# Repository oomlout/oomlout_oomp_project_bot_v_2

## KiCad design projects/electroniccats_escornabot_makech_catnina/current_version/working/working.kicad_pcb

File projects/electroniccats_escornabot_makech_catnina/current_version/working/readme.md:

# escornabot_makech
 
## summary 
* id: electroniccats_escornabot_makech_catnina
* user: electroniccats
* name: escornabot_makech
* board: catnina
* repo: https://github.com/ElectronicCats/Escornabot-Makech
* src_file_repo_kicad_pcb: Makech/Expansion NINA/CatNINA.kicad_pcb
* src_file_repo_kicad_pcb_link: https://github.com/ElectronicCats/Escornabot-Makech/tree/master/Makech/Expansion NINA/CatNINA.kicad_pcb

* src_file_repo_sch: Makech/Expansion NINA/CatNINA.sch
* src_file_repo_sch_link: https://github.com/ElectronicCats/Escornabot-Makech/tree/master/Makech/Expansion NINA/CatNINA.sch
* full details link: https://github.com/oomlout/oomlout_oomp_project_bot_v_2/tree/main/projects/electroniccats_escornabot_makech_catnina/current_version/working

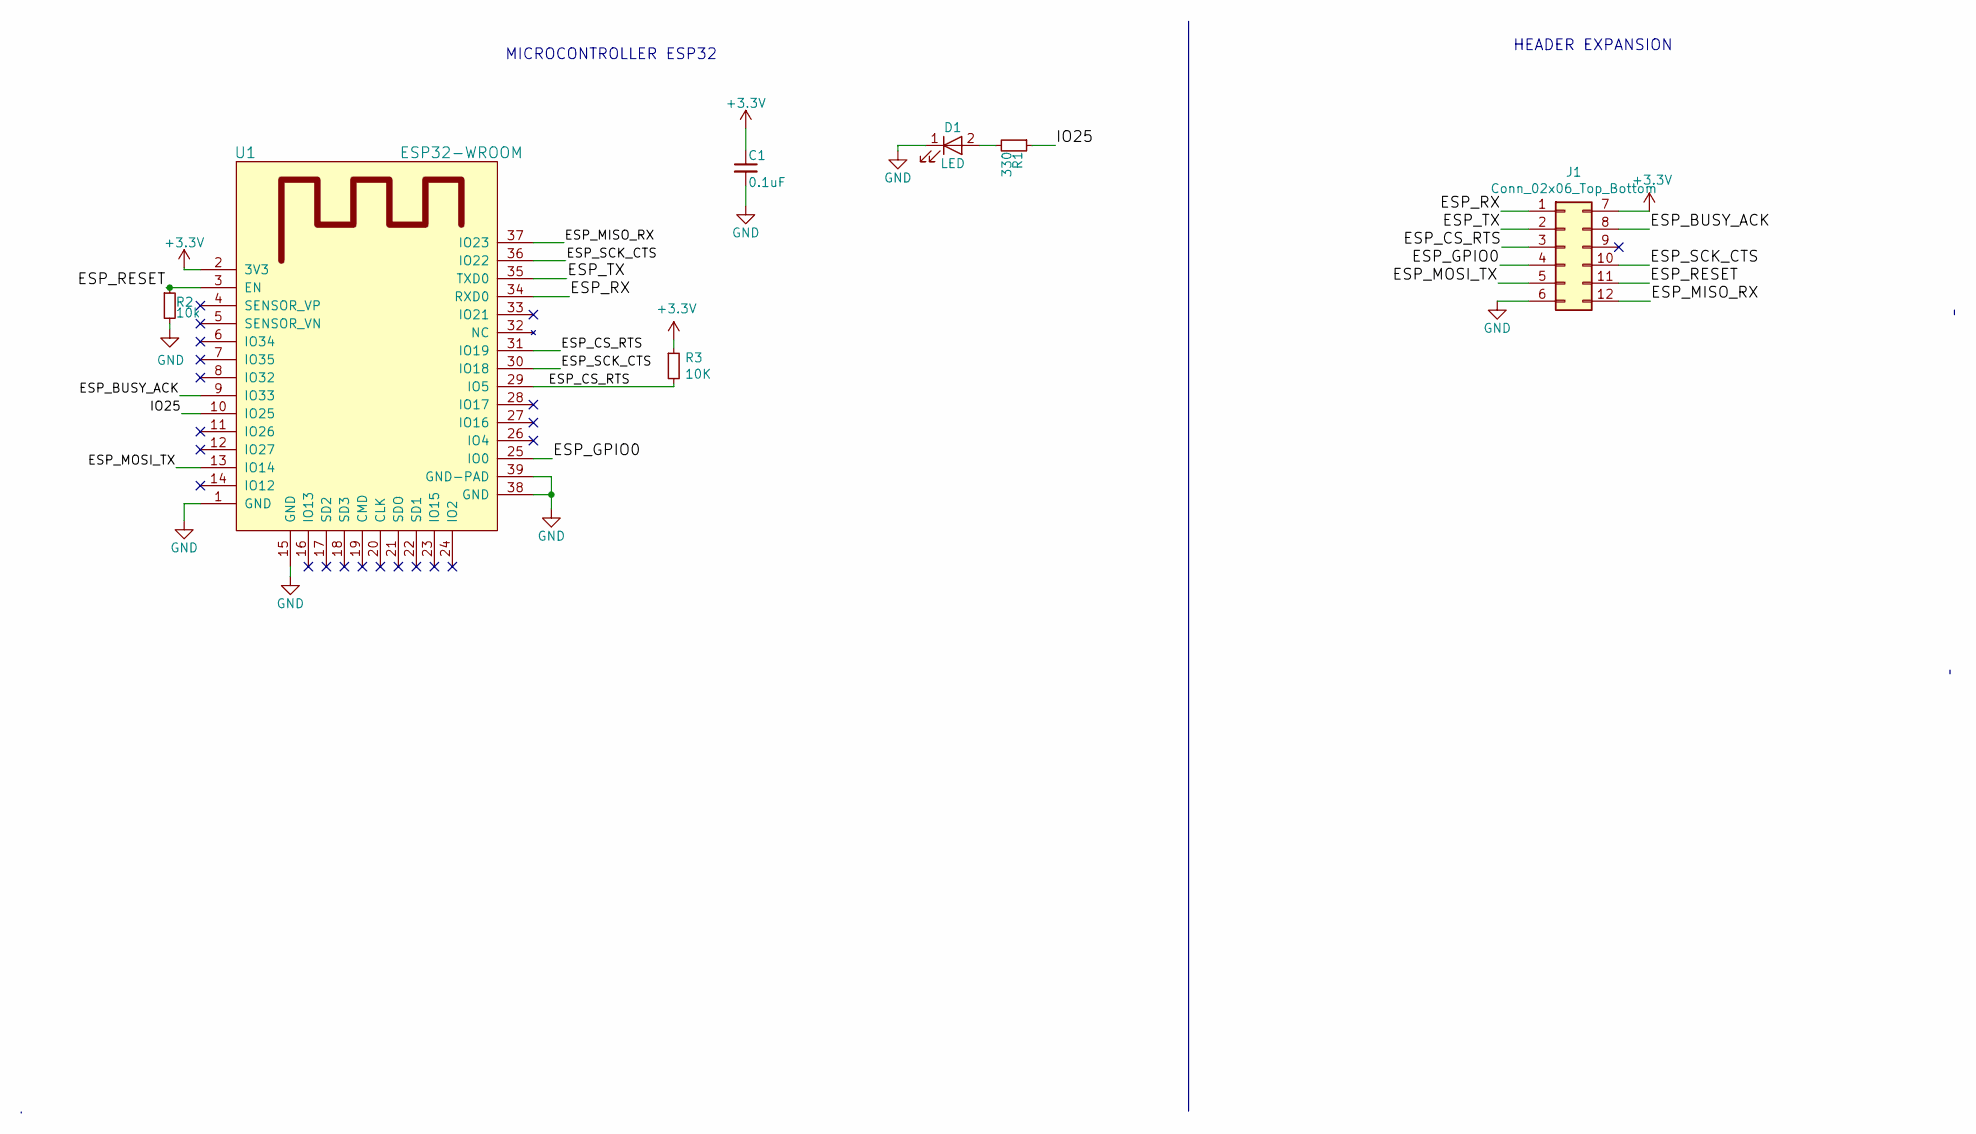
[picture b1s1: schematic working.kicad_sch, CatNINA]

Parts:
C1: 0.1uF; C_0805_HandSoldering
D1: LED; LED_0805_HandSoldering
J1: Conn_02x06_Top_Bottom; 61301221121
R1: 330; R_0805_HandSoldering
R2: 10k; R_0805_HandSoldering
R3: 10K; R_0805_HandSoldering
U1: ESP32-WROOM

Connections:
+3V3: C1.1, J1.7, R3.1, U1.2 (3V3)
/ESP_BUSY_ACK: J1.8, U1.9 (IO33)
/ESP_CS_RTS: J1.3, R3.2, U1.29 (IO5), U1.31 (IO19)
/ESP_GPIO0: J1.4, U1.25 (IO0)
/ESP_MISO_RX: J1.12, U1.37 (IO23)
/ESP_MOSI_TX: J1.5, U1.13 (IO14)
/ESP_RESET: J1.11, R2.1, U1.3 (EN)
/ESP_RX: J1.1, U1.34 (RXD0)
/ESP_SCK_CTS: J1.10, U1.30 (IO18), U1.36 (IO22)
/ESP_TX: J1.2, U1.35 (TXD0)
/IO25: R1.1, U1.10 (IO25)
GND: C1.2, D1.1 (K), J1.6, R2.2, U1.1 (GND), U1.15 (GND), U1.38 (GND), U1.39 (GND-PAD)
unnamed: D1.2 (A), R1.2

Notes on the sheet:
MICROCONTROLLER ESP32
HEADER EXPANSION

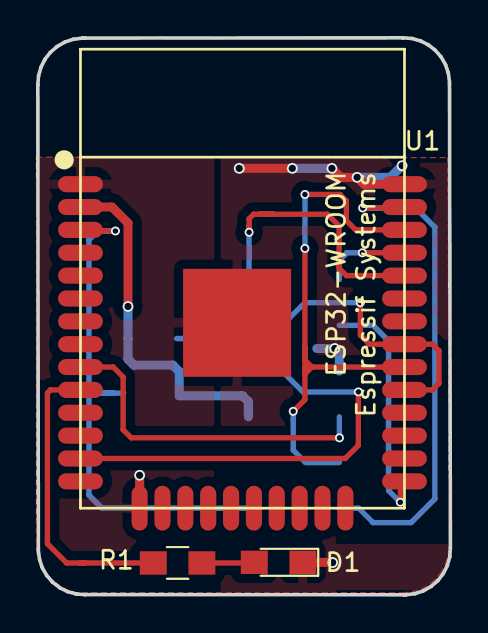
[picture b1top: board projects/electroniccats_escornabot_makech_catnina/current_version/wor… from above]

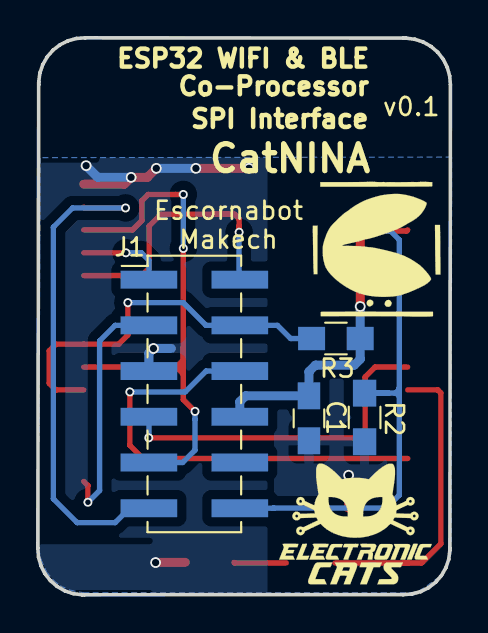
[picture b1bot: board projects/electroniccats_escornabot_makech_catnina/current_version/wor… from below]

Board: 2 copper layers, 22.9 x 30.9 mm, 7 parts (4 on the bottom side), 13 nets.

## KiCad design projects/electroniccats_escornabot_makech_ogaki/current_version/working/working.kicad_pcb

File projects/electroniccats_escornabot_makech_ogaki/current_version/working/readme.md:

# escornabot_makech
 
## summary 
* id: electroniccats_escornabot_makech_ogaki
* user: electroniccats
* name: escornabot_makech
* board: ogaki
* repo: https://github.com/ElectronicCats/Escornabot-Makech
* src_file_repo_kicad_pcb: Ogaki/hardware/KiCad files/Ogaki.kicad_pcb
* src_file_repo_kicad_pcb_link: https://github.com/ElectronicCats/Escornabot-Makech/tree/master/Ogaki/hardware/KiCad files/Ogaki.kicad_pcb

* src_file_repo_sch: Ogaki/hardware/KiCad files/Ogaki.sch
* src_file_repo_sch_link: https://github.com/ElectronicCats/Escornabot-Makech/tree/master/Ogaki/hardware/KiCad files/Ogaki.sch
* full details link: https://github.com/oomlout/oomlout_oomp_project_bot_v_2/tree/main/projects/electroniccats_escornabot_makech_ogaki/current_version/working

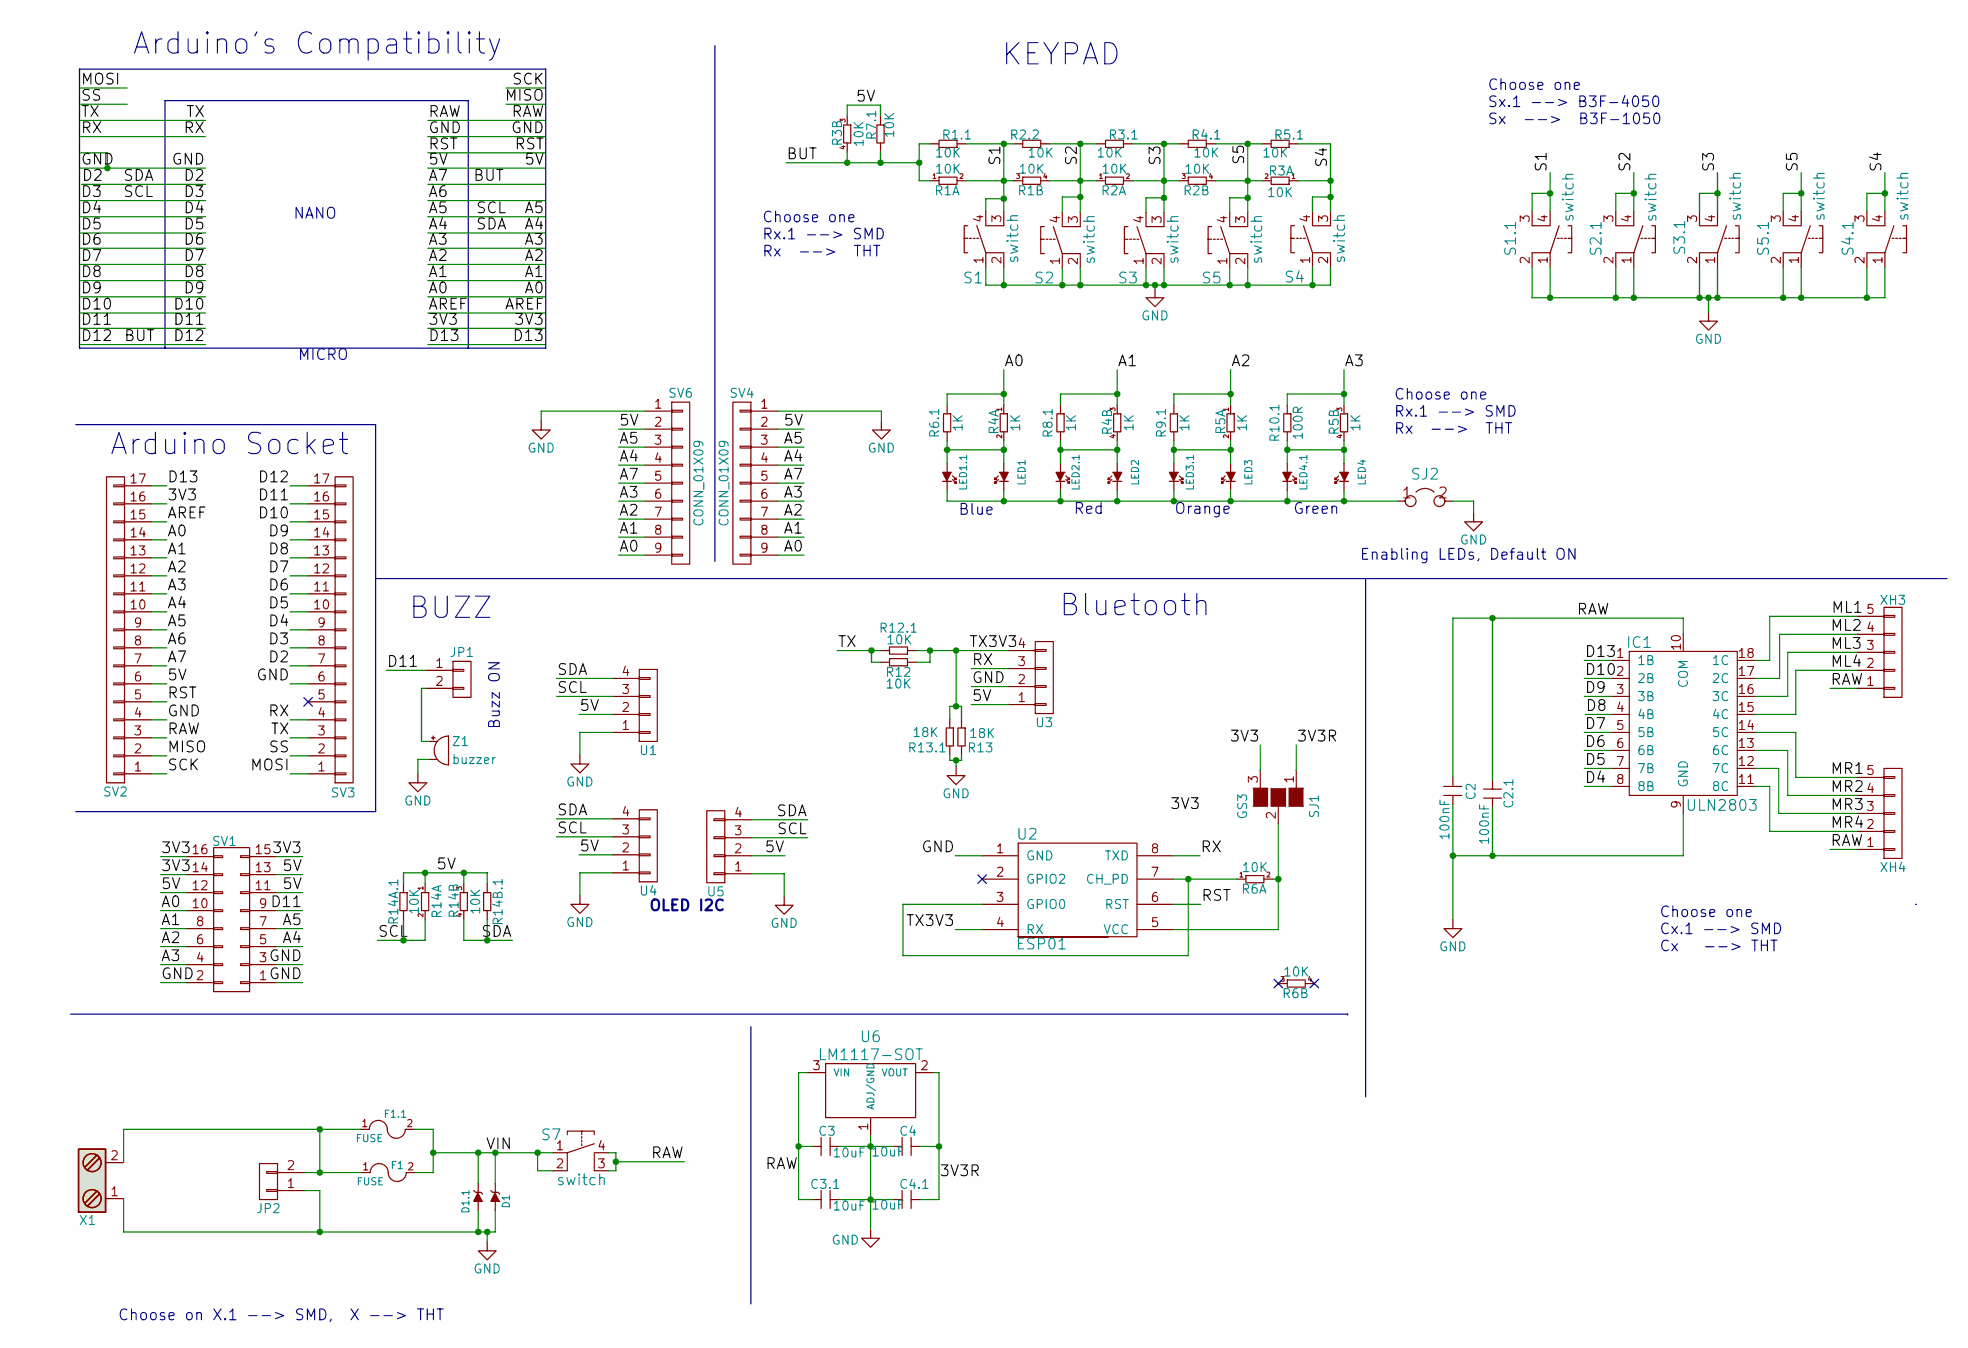
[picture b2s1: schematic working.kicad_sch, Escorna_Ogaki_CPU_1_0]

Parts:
C2: 100nF; C_Disc_D5.0mm_W2.5mm_P5.00mm
C2.1: 100nF; C_0603_HandSoldering
C3, C4: 10uF; C_Disc_D5.0mm_W2.5mm_P5.00mm
C3.1, C4.1: 10uF; C_0603_HandSoldering
D1: ZENER; D_DO-41_SOD81_P10.16mm_Horizontal
D1.1: ZENER; D_0603
F1: FUSE; Fuse_TE5_Littlefuse-395Series
F1.1: FUSE; R_1206_HandSoldering
IC1: ULN2803; DIP-18_W7.62mm_Socket
JP1: CONN_01X02; Pin_Header_Straight_1x02_Pitch2.54mm
JP2: CONN_01X02; Pin_Header_Angled_1x02_Pitch2.54mm
LED1, LED2, LED3, LED4: L; LED_D3.0mm
LED1.1, LED2.1, LED3.1, LED4.1: L; LED_0603
R1, R2, R3, R6, R14: 10K; R_Array_SIP4
R1.1, R2.2, R3.1, R4.1, R5.1, R7.1, R12.1, R14A.1, R14B.1: 10K; R_0603_HandSoldering
R4, R5: 1K; R_Array_SIP4
R6.1, R8.1, R9.1: 1K; R_0603_HandSoldering
R10.1: 100R; R_0603_HandSoldering
R12: 10K; R_Axial_DIN0204_L3.6mm_D1.6mm_P7.62mm_Horizontal
R13: 18K; R_Axial_DIN0204_L3.6mm_D1.6mm_P7.62mm_Horizontal
R13.1: 18K; R_0603_HandSoldering
S1, S2, S3, S4, S5: switch; Button
S1.1, S2.1, S3.1, S4.1, S5.1: switch; SW_PUSH_6mm
S7: switch; on_off_Switch
SJ1: GS3
SJ2: JUMPER; GS2
SV1: CONN_02X08; Pin_Header_Straight_2x08_Pitch2.54mm
SV2, SV3: CONN_01X17; Pin_Header_Straight_1x17_Pitch2.54mm
SV4, SV6: CONN_01X09; Pin_Header_Straight_1x09_Pitch2.54mm
U1, U3, U4, U5: CONN_01X04; Pin_Header_Straight_1x04_Pitch2.54mm
U2: ESP01
U6: LM1117-SOT; TO-220_Vertical
X1: Screw_Terminal_1x02; bornier2
XH3, XH4: CONN_01X05; B5B-XH-A
Z1: buzzer; MagneticBuzzer_StarMicronics_HMB-06_HMB-12

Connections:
/3V3: SJ1.3 (G3), SV1.14, SV1.15, SV1.16, SV2.16
/3V3R: C4.1, C4.1.1, SJ1.1 (G1), U6.2 (VOUT)
/5V: R3.3, R7.1.1, R14.1, R14.3, R14A.1.1, R14B.1.1, SV1.11, SV1.12, SV1.13, SV2.6, SV4.2, SV6.2, U1.2, U3.1, U4.2, U5.2
/A0: R4.1, R6.1.1, SV1.10, SV2.14, SV4.9, SV6.9
/A1: R4.3, R8.1.1, SV1.8, SV2.13, SV4.8, SV6.8
/A2: R5.1, R9.1.1, SV1.6, SV2.12, SV4.7, SV6.7
/A3: R5.3, R10.1.1, SV1.4, SV2.11, SV4.6, SV6.6
/A4: R14.4, R14B.1.2, SV1.5, SV2.10, SV3.7, SV4.4, SV6.4, U1.4, U4.4, U5.4
/A5: R14.2, R14A.1.2, SV1.7, SV2.9, SV3.8, SV4.3, SV6.3, U1.3, U4.3, U5.3
/A6: SV2.8
/A7: R1.1, R1.1.2, R3.4, R7.1.2, SV2.7, SV3.17, SV4.5, SV6.5
/AREF: SV2.15
/D4: IC1.8 (8B), SV3.9
/D5: IC1.7 (7B), SV3.10
/D6: IC1.6 (6B), SV3.11
/D7: IC1.5 (5B), SV3.12
/D8: IC1.4 (4B), SV3.13
/D9: IC1.3 (3B), SV3.14
/D10: IC1.2 (2B), SV3.15
/D11: JP1.1, SV1.9, SV3.16
/D13: IC1.1 (1B), SV2.17
/MISO: SV2.2
/ML1: IC1.18 (1C), XH3.5
/ML2: IC1.17 (2C), XH3.4
/ML3: IC1.16 (3C), XH3.3
/ML4: IC1.15 (4C), XH3.2
/MOSI: SV3.1
/MR1: IC1.14 (5C), XH4.5
/MR2: IC1.13 (6C), XH4.4
/MR3: IC1.12 (7C), XH4.3
/MR4: IC1.11 (8C), XH4.2
/RAW: C2.2, C2.1.2, C3.2, C3.1.2, IC1.10 (COM), S7.3, S7.4, SV2.3, U6.3 (VIN), XH3.1, XH4.1
/RST: SV2.5, U2.6 (RST)
/RX: SV3.4, U2.8 (TXD), U3.3
/S1: R1.2, R1.3, R1.1.1, R2.2.2, S1.3, S1.4, S1.1.3, S1.1.4
/S2: R1.4, R2.1, R2.2.1, R3.1.2, S2.3, S2.4, S2.1.3, S2.1.4
/S3: R2.2, R2.3, R3.1.1, R4.1.2, S3.3, S3.4, S3.1.3, S3.1.4
/S4: R3.1, R5.1.1, S4.3, S4.4, S4.1.3, S4.1.4
/S5: R2.4, R3.2, R4.1.1, R5.1.2, S5.3, S5.4, S5.1.3, S5.1.4
/SCK: SV2.1
/SS: SV3.2
/TX: R12.2, R12.1.2, SV3.3
/TX3V3: R12.1, R12.1.1, R13.1, R13.1.1, U2.4 (RX), U3.4
/VIN: D1.1 (K), D1.1.1 (K), F1.2, F1.1.2, S7.1, S7.2
GND: C2.1, C2.1.1, C3.1, C3.1.1, C4.2, C4.1.2, D1.2 (A), D1.1.2 (A), IC1.9 (GND), JP2.1, R13.2, R13.1.2, S1.1, S1.2, S1.1.1, S1.1.2, S2.1, S2.2, S2.1.1, S2.1.2, S3.1, S3.2, S3.1.1, S3.1.2, S4.1, S4.2, S4.1.1, S4.1.2, S5.1, S5.2, S5.1.1, S5.1.2, SJ2.2, SV1.1, SV1.2, SV1.3, SV2.4, SV3.6, SV4.1, SV6.1, U1.1, U2.1 (GND), U3.2, U4.1, U5.1, U6.1 (ADJ/GND), X1.1, Z1.2; also elsewhere on the board
unnamed: F1.1, F1.1.1, JP2.2, X1.2
unnamed: JP1.2, Z1.1
unnamed: LED1.1 (K), LED1.1.1 (K), LED2.1 (K), LED2.1.1 (K), LED3.1 (K), LED3.1.1 (K), LED4.1 (K), LED4.1.1 (K), SJ2.1
unnamed: LED1.2 (A), LED1.1.2 (A), R4.2, R6.1.2
unnamed: LED2.2 (A), LED2.1.2 (A), R4.4, R8.1.2
unnamed: LED3.2 (A), LED3.1.2 (A), R5.2, R9.1.2
unnamed: LED4.2 (A), LED4.1.2 (A), R5.4, R10.1.2
unnamed: R6.1, U2.3 (GPIO0), U2.7 (CH_PD)
unnamed: R6.2, SJ1.2 (G2), U2.5 (VCC)

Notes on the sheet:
OLED I2C
Choose one Cx.1 --> SMD Cx --> THT
Choose one Rx.1 --> SMD Rx --> THT
Green
Red
Choose on X.1 --> SMD, X --> THT
MICRO
KEYPAD
Enabling LEDs, Default ON
NANO
Choose one Sx.1 --> B3F-4050 Sx --> B3F-1050
Bluetooth
Arduino Socket
BUZZ
Orange
Buzz ON
Arduino's Compatibility
Blue

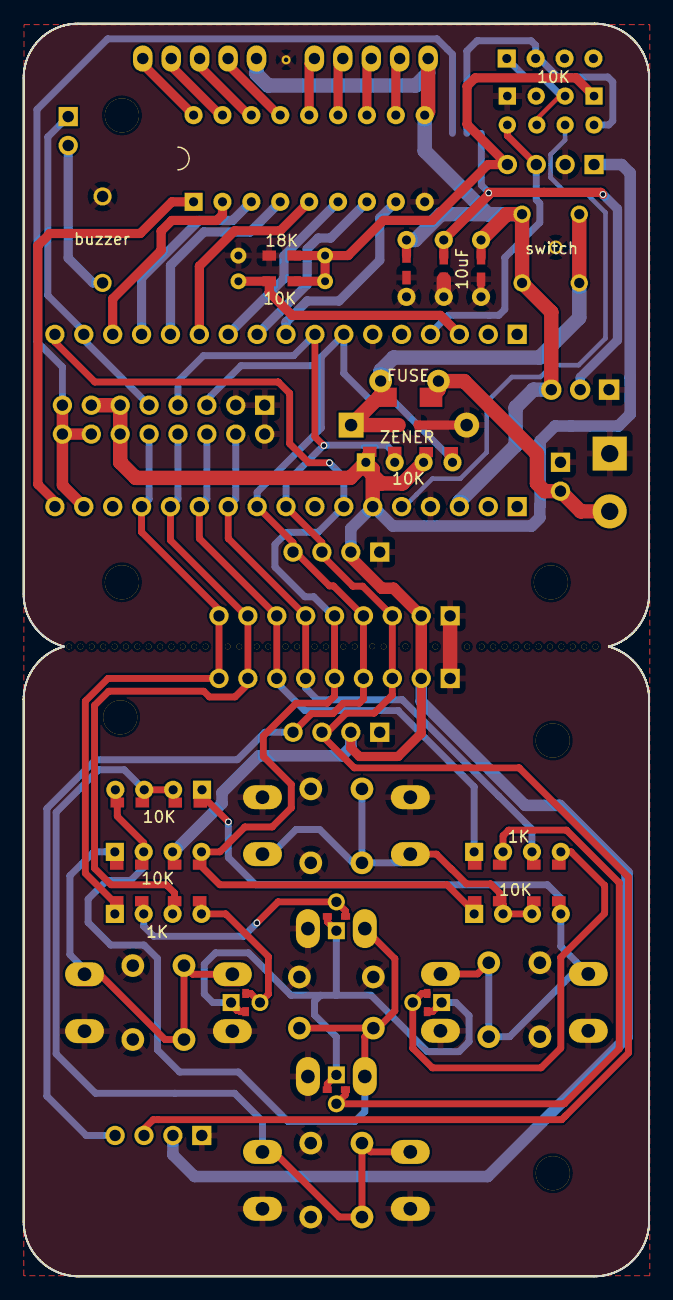
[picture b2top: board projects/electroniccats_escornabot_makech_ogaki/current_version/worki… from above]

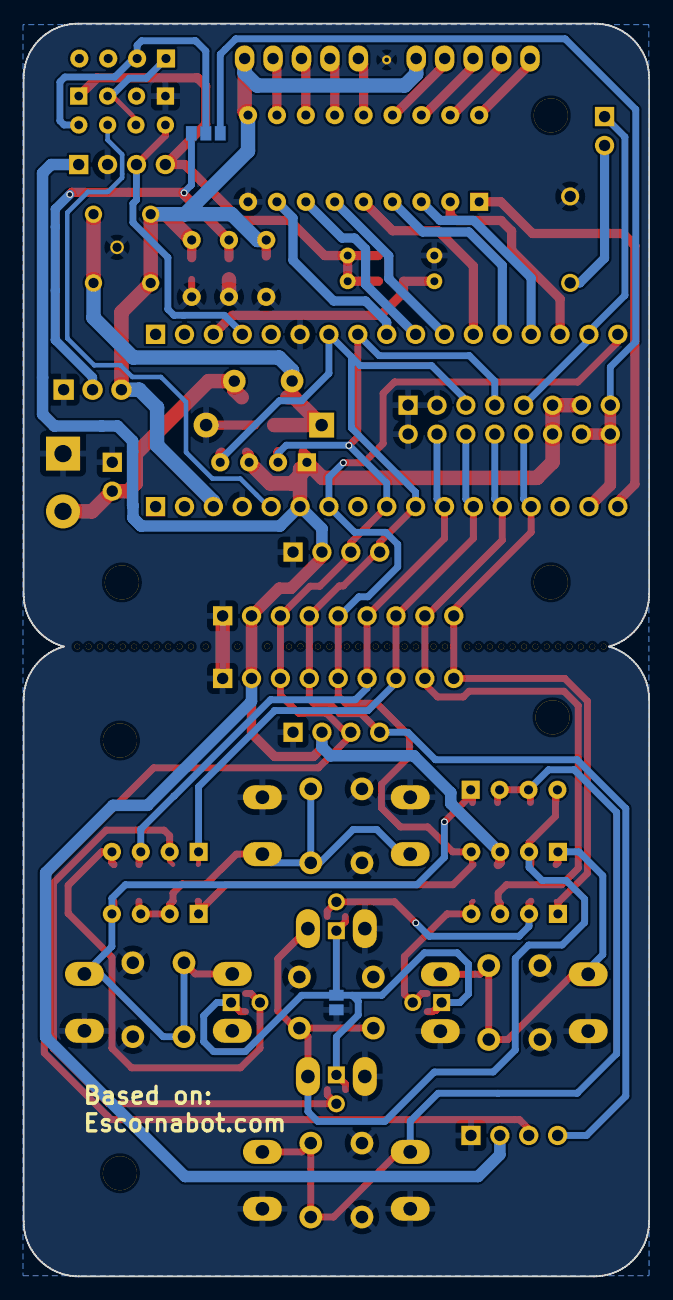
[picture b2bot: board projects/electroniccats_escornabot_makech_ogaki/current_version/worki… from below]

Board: 2 copper layers, 55.0 x 110.1 mm, 75 parts (3 on the bottom side), 48 nets.

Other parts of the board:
GND: GND; SolderWirePad_single_0-8mmDrill
svg2mod, svg2mod#2: G***; svg2mod

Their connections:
GND: GND.1; also elsewhere on the board

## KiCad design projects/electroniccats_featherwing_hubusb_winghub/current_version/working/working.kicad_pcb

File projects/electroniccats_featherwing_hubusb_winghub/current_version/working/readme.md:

# featherwing_hubusb
 
## summary 
* id: electroniccats_featherwing_hubusb_winghub
* user: electroniccats
* name: featherwing_hubusb
* board: winghub
* repo: https://github.com/ElectronicCats/FeatherWing-HUBUSB
* src_file_repo_kicad_pcb: Hardware/WingHub.kicad_pcb
* src_file_repo_kicad_pcb_link: https://github.com/ElectronicCats/FeatherWing-HUBUSB/tree/master/Hardware/WingHub.kicad_pcb

* src_file_repo_sch: Hardware/WingHub.sch
* src_file_repo_sch_link: https://github.com/ElectronicCats/FeatherWing-HUBUSB/tree/master/Hardware/WingHub.sch
* full details link: https://github.com/oomlout/oomlout_oomp_project_bot_v_2/tree/main/projects/electroniccats_featherwing_hubusb_winghub/current_version/working

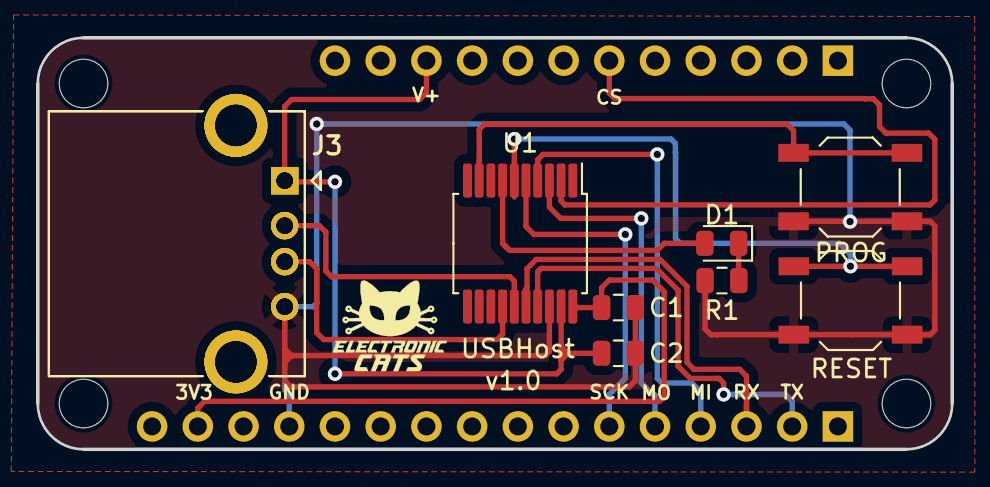
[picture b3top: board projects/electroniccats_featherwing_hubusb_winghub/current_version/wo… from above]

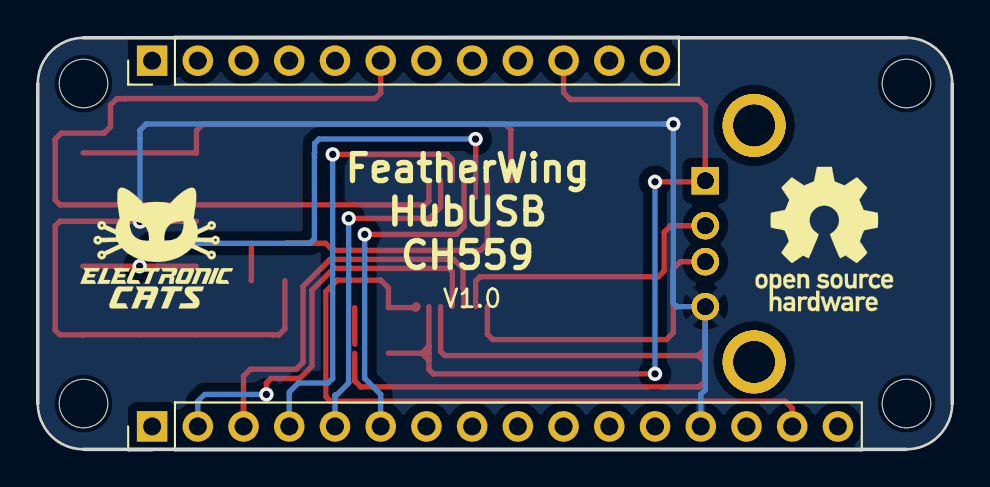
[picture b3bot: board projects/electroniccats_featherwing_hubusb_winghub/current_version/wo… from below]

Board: 2 copper layers, 50.8 x 22.9 mm, 11 parts (2 on the bottom side), 16 nets.

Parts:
C1: 0.1uF; C_0805_2012Metric
C2: 3.3uF; C_0805_2012Metric
D1: LED; LED_0805_2012Metric
J1: feather long; PinHeader_1x16_P2.54mm_Vertical
J2: feather short; PinHeader_1x12_P2.54mm_Vertical
J3, J3#2: USB_A; USB_A_CONNFLY_DS1095-WNR0
PROG: DOWNLOADER; SW_SPST_TL3342
R1: 1K; R_0805_2012Metric
RESET: RESET; SW_SPST_TL3342
U1: CH559T; SSOP-20_5.3x7.2mm_P0.65mm

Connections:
+3V3: C1.1, J1.15, U1.20
/CS: J2.6, U1.2
/D+: J3.3, J3#2.3, U1.14
/D-: J3.2, J3#2.2, U1.15
/LED: D1.2, U1.7
/MISO: J1.4, U1.4
/MOSI: J1.5, U1.3
/PROG: PROG.1, U1.9
/RST: RESET.1, U1.6
/RX: J1.3, U1.16
/SCK: J1.6, U1.5
/TX: J1.2, U1.17
GND: C1.2, C2.2, J1.13, J3.4, J3#2.4, PROG.2, R1.2, RESET.2, U1.18
unnamed: D1.1, R1.1
unnamed: J3.5, J3#2.5
VBUS: C2.1, J2.10, J3.1, J3#2.1, U1.19

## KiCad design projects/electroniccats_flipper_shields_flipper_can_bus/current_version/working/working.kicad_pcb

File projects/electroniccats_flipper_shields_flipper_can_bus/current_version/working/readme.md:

# flipper_shields
 
## summary 
* id: electroniccats_flipper_shields_flipper_can_bus
* user: electroniccats
* name: flipper_shields
* board: flipper_can_bus
* repo: https://github.com/ElectronicCats/flipper-shields
* src_file_repo_kicad_pcb: FLIPPER_CAN_BUS/FLIPPER_CAN_BUS.kicad_pcb
* src_file_repo_kicad_pcb_link: https://github.com/ElectronicCats/flipper-shields/tree/main/FLIPPER_CAN_BUS/FLIPPER_CAN_BUS.kicad_pcb
* src_file_repo_kicad_sch: FLIPPER_CAN_BUS/FLIPPER_CAN_BUS.kicad_sch
* src_file_repo_kicad_sch_link: https://github.com/ElectronicCats/flipper-shields/tree/main/FLIPPER_CAN_BUS/FLIPPER_CAN_BUS.kicad_sch

* src_file_repo_sch: 
* src_file_repo_sch_link: https://github.com/ElectronicCats/flipper-shields/tree/main/
* full details link: https://github.com/oomlout/oomlout_oomp_project_bot_v_2/tree/main/projects/electroniccats_flipper_shields_flipper_can_bus/current_version/working

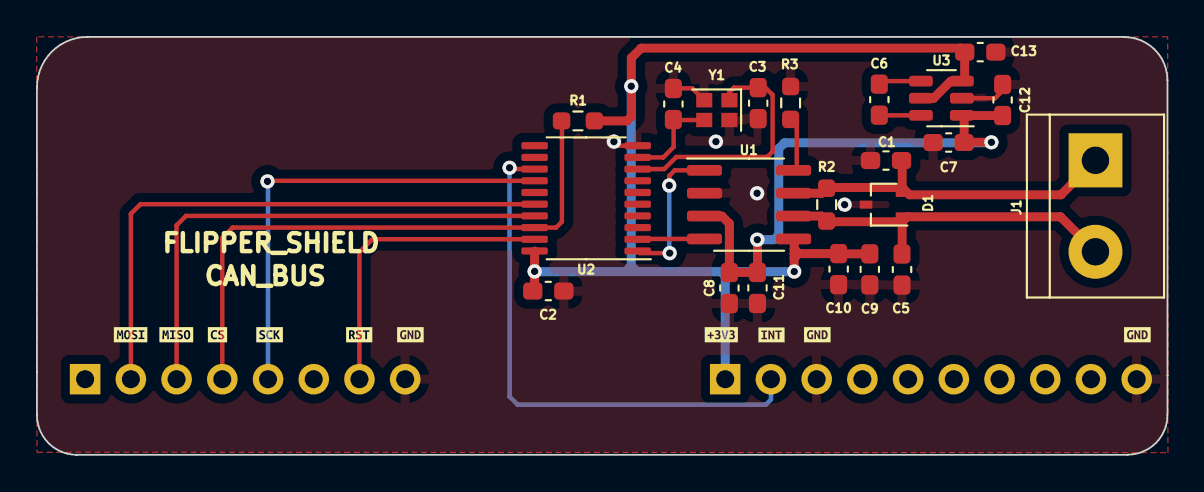
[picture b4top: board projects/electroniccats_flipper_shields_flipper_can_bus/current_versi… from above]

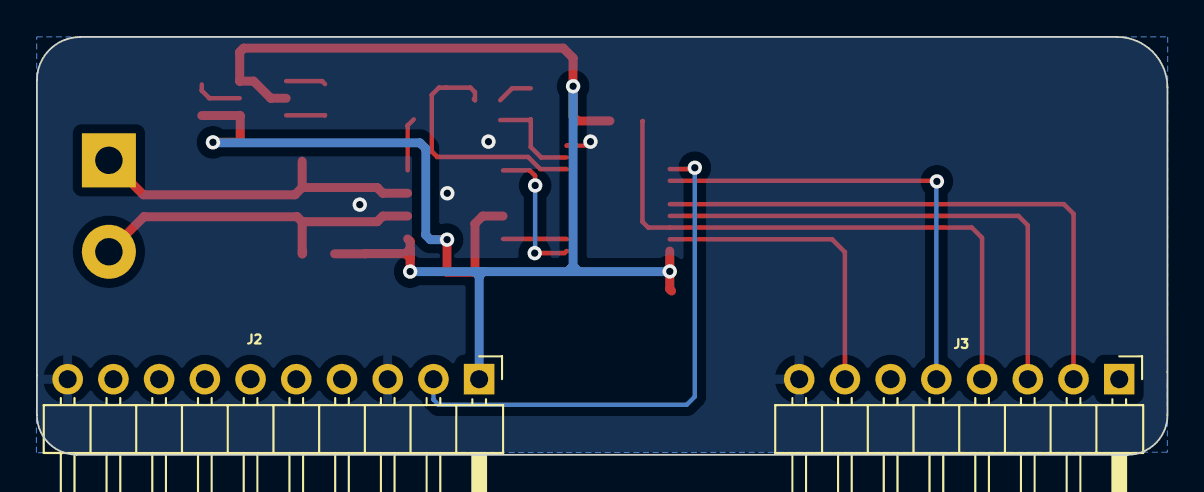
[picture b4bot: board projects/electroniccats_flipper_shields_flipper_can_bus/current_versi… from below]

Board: 2 copper layers, 62.8 x 23.2 mm, 34 parts (2 on the bottom side), 18 nets.

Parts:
C1, C5: 47pf; C_0603_1608Metric_Pad1.08x0.95mm_HandSolder
C2, C7, C9, C11: 0.1uf; C_0603_1608Metric_Pad1.08x0.95mm_HandSolder
C3, C4: 22pf; C_0603_1608Metric_Pad1.08x0.95mm_HandSolder
C6: 1uf; C_0603_1608Metric_Pad1.08x0.95mm_HandSolder
C8, C10, C12, C13: 10uf; C_0603_1608Metric_Pad1.08x0.95mm_HandSolder
D1: PESD1CAN; SOT-323_SC-70
J1: Conn_01x02; TerminalBlock_bornier-2_P5.08mm
J2: Conn_01x10_Socket; PinHeader_1x10_P2.54mm_Horizontal
J3: Conn_01x08_Socket; PinHeader_1x08_P2.54mm_Horizontal
R1, R3: 10k; R_0603_1608Metric_Pad0.98x0.95mm_HandSolder
R2: 120; R_0603_1608Metric_Pad0.98x0.95mm_HandSolder
U1: TJA1051T/3; SOIC-8_3.9x4.9mm_P1.27mm
U2: MCP2515-xST; TSSOP-20_4.4x6.5mm_P0.65mm
U3: AP3602AKTR-G1; TSOT-23-6
Y1: 16 Mhz; Crystal_SMD_2016-4Pin_2.0x1.6mm
kibuzzard-644AD5B8: G***; kibuzzard-644AD5B8
kibuzzard-644AD5D8: G***; kibuzzard-644AD5D8
kibuzzard-644AD5FD, kibuzzard-644AD5FD#2, kibuzzard-644AD5FD#3: G***; kibuzzard-644AD5FD
kibuzzard-644AD57B: G***; kibuzzard-644AD57B
kibuzzard-644AD570: G***; kibuzzard-644AD570
kibuzzard-644AD586: G***; kibuzzard-644AD586
kibuzzard-644AD591: G***; kibuzzard-644AD591
kibuzzard-644AD616: G***; kibuzzard-644AD616

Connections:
+3V3: C2.2, C9.1, C10.1, C13.1, J2.1, R1.1, U1.5 (VI/O), U2.20 (VDD), U3.3 (*SHDN), U3.5 (VIN)
+5V: C7.1, C8.1, C11.1, C12.1, U1.3 (VCC), U3.1 (VOUT)
/CAN_H: C1.1, D1.2, J1.1, R2.2, U1.7 (CANH)
/CAN_L: C5.2, D1.1, J1.2, R2.1, U1.6 (CANL)
/CS: J3.4, R1.2, U2.18 (~CS)
/INT: J2.2, U2.13 (~INT)
/MISO: J3.3, U2.17 (SO)
/MOSI: J3.2, U2.16 (SI)
/RST: J3.7, U2.19 (~RESET)
/RXD: U1.4 (RXD), U2.2 (RXCAN)
/SCK: J3.5, U2.14 (SCK)
/TXD: U1.1 (TXD), U2.1 (TXCAN)
GND: C1.2, C2.1, C3.1, C4.1, C5.1, C7.2, C8.2, C9.2, C10.2, C11.2, C12.2, C13.2, D1.3, J2.3, J2.10, J3.8, R3.1, U1.2 (GND), U2.10 (VSS), U3.2 (GND), Y1.2, Y1.4
unnamed: R3.2, U1.8 (S)
unnamed: C4.2, U2.9 (OSC1), Y1.3
unnamed: C3.2, U2.8 (OSC2), Y1.1
unnamed: C6.1, U3.6 (C+)
unnamed: C6.2, U3.4 (C-)

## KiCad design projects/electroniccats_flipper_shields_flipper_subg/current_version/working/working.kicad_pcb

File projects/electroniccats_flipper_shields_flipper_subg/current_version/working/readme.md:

# flipper_shields
 
## summary 
* id: electroniccats_flipper_shields_flipper_subg
* user: electroniccats
* name: flipper_shields
* board: flipper_subg
* repo: https://github.com/ElectronicCats/flipper-shields
* src_file_repo_kicad_pcb: FLIPPER_Subg/Flipper_subg.kicad_pcb
* src_file_repo_kicad_pcb_link: https://github.com/ElectronicCats/flipper-shields/tree/main/FLIPPER_Subg/Flipper_subg.kicad_pcb
* src_file_repo_kicad_sch: FLIPPER_Subg/Flipper_subg.kicad_sch
* src_file_repo_kicad_sch_link: https://github.com/ElectronicCats/flipper-shields/tree/main/FLIPPER_Subg/Flipper_subg.kicad_sch

* src_file_repo_sch: 
* src_file_repo_sch_link: https://github.com/ElectronicCats/flipper-shields/tree/main/
* full details link: https://github.com/oomlout/oomlout_oomp_project_bot_v_2/tree/main/projects/electroniccats_flipper_shields_flipper_subg/current_version/working

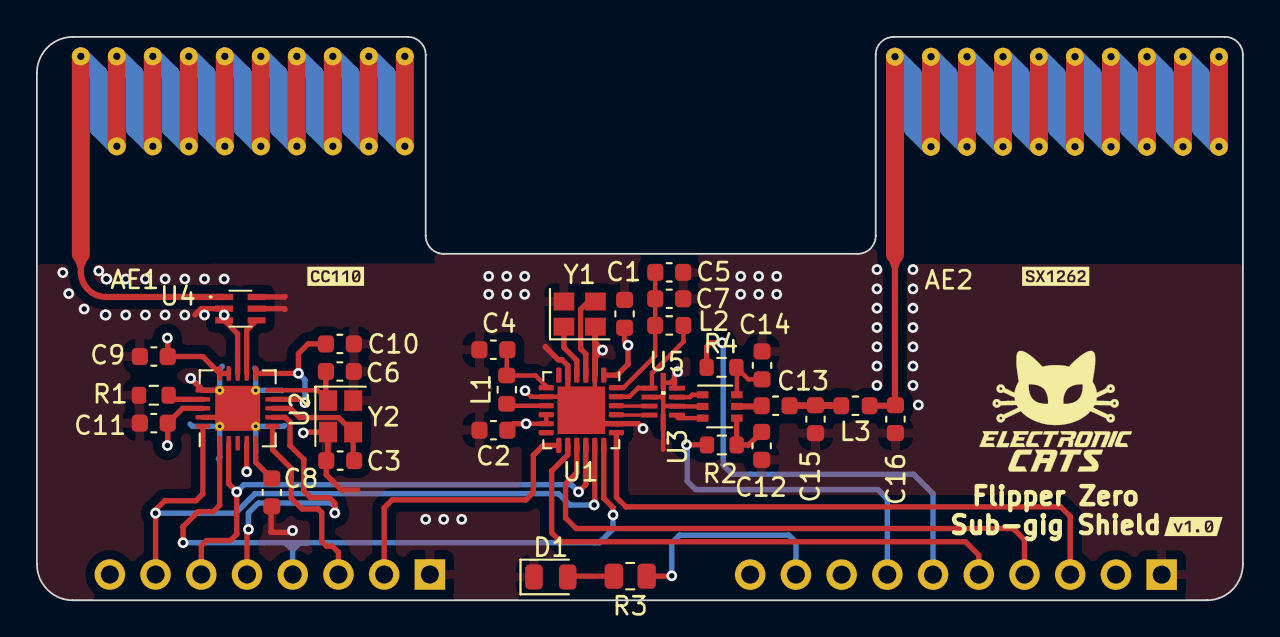
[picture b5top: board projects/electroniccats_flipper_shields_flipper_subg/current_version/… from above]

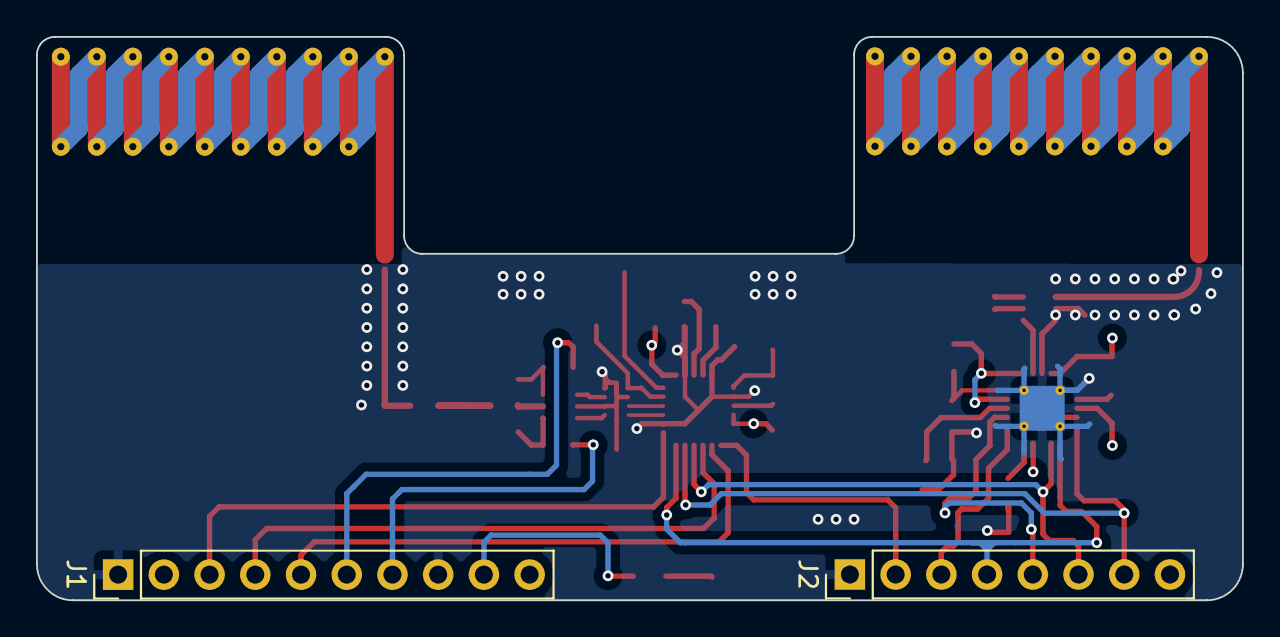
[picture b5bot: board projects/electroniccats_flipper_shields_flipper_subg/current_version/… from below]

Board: 4 copper layers, 67.0 x 31.3 mm, 38 parts (2 on the bottom side), 37 nets.

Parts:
AE1, AE2: Antenna; Texas_SWRA416_868MHz_915MHz
C1, C2, C5, C8, C9, C10: 0.1uF; C_0603_1608Metric
C3, C6: uF; C_0603_1608Metric
C4: 470nF; C_0603_1608Metric
C7: 47pF; C_0603_1608Metric
C11: 10uF; C_0603_1608Metric
C12, C14: 1nF; C_0603_1608Metric
C13: 100pF; C_0603_1608Metric
C15, C16: 3.3pF; C_0603_1608Metric
D1: LED; LED_0805_2012Metric
J1: Conn_01x10_Socket; PinHeader_1x10_P2.54mm_Vertical
J2: Conn_01x08_Socket; PinHeader_1x08_P2.54mm_Vertical
L1: 15uH; L_0603_1608Metric
L2: 47nH; L_0603_1608Metric
L3: 9.1nH; L_0603_1608Metric
R1: 56K; R_0603_1608Metric
R2, R4: 100R; R_0603_1608Metric
R3: 1K; R_0805_2012Metric
U1: SX1262IMLTRT; QFN-24-1EP_4x4mm_P0.5mm_EP2.65x2.65mm
U2: CC1101RGPR; QFN-20-1EP_4x4mm_P0.5mm_EP2.5x2.5mm_ThermalVias
U3: 0900FM15D0039; 0900FM15D0039E
U4: 0915BM15A0001E
U5: PE42421; SOT-363_SC-70-6
Y1: 32Mhz; Crystal_SMD_2520-4Pin_2.5x2.0mm
Y2: 24Mhz; Crystal_SMD_2520-4Pin_2.5x2.0mm
kibuzzard-649F73CE: G***; kibuzzard-649F73CE
kibuzzard-649F737D: G***; kibuzzard-649F737D
kibuzzard-649F739B: G***; kibuzzard-649F739B

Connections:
+3.3V: C1.1, C2.1, C9.1, C10.1, C11.1, J1.10, U1.1 (VDD_IN), U1.10 (VBAT), U1.11 (VBAT_IO), U2.4 (DVDD), U2.9 (AVDD_1), U2.11 (AVDD_2), U2.14 (AVDD_3), U2.15 (AVDD_4), U2.18 (DGUARD)
/ANT_SW: J1.6, R4.2
/BUSY: J1.5, U1.14 (BUSY)
/CIPO: J2.6, U1.16 (MISO), U2.2 (SO_(GDO1))
/COPI: J2.7, U1.17 (MOSI), U2.20 (SI)
/DIO1: J2.2, U1.13 (DIO1)
/DIO22: J1.7, R2.2
/GDO0: J2.3, U2.6 (GDO0_(ATEST))
/LED1: J1.9, R3.1
/NSS: J2.5, U2.7 (CSN)
/NSS_1: J1.3, U1.19 (NSS)
/RESET_SX: J1.4, U1.15 (~NRESET)
/RFI_N: U1.22 (RFI_N), U3.3 (RFI_N)
/RFI_P: U1.21 (RFI_P), U3.4 (RFI_P)
/RFO: L2.2, U1.23 (RFO), U3.1 (RFO)
/SCK: J2.4, U1.18 (SCK), U2.1 (SCLK)
/SW_RFI: U3.6 (SW_RFI), U5.3 (RF2)
/SW_RFO: U3.8 (SW_RFO), U5.1 (RF1)
/XTA: U1.3 (XTA), Y1.3
/XTB: U1.4 (XTB), Y1.1
GND: C1.2, C2.2, C3.2, C4.2, C5.2, C6.2, C7.2, C8.2, C9.2, C10.2, C11.2, C12.2, C14.2, C15.2, C16.2, D1.1 (K), J1.1, J1.8, J2.1, R1.1, U1.2 (GND), U1.5 (GND), U1.8 (GND), U1.20 (GND), U1.25 (EXP), U2.16 (GND_1), U2.19 (GND_2), U2.21 (GND_3), U3.2 (GND), U3.5 (GND), U3.7 (GND), U3.9 (GND), U3.10 (GND), U4.2 (GND), U4.5 (GND_2), U4.6 (GND_3), U5.2 (GND), Y1.2, Y1.4, Y2.2, Y2.4
unnamed: AE1.1 (A), U4.1 (OUT)
unnamed: AE2.1 (A), C16.1, L3.1
unnamed: C13.2, C15.1, L3.2
unnamed: D1.2 (A), R3.2
unnamed: L1.1, U1.9 (DCC_SW)
unnamed: C4.1, L1.2, U1.7 (VREG)
unnamed: C5.1, C7.1, L2.1, U1.24 (VR_PA)
unnamed: C8.1, U2.5 (DCOUPL)
unnamed: R1.2, U2.17 (RBIAS)
unnamed: U2.13 (RF_N), U4.3 (IN1)
unnamed: U2.12 (RF_P), U4.4 (IN2)
unnamed: C3.1, U2.8 (XOSC_Q1), Y2.3
unnamed: C6.1, U2.10 (XOSC_Q2), Y2.1
unnamed: C13.1, U5.5 (RFC)
unnamed: C14.1, R4.1, U5.6 (V1)
unnamed: C12.1, R2.1, U5.4 (V2)

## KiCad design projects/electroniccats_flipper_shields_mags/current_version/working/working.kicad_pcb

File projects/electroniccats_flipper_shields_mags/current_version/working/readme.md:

# flipper_shields
 
## summary 
* id: electroniccats_flipper_shields_mags
* user: electroniccats
* name: flipper_shields
* board: mags
* repo: https://github.com/ElectronicCats/flipper-shields
* src_file_repo_kicad_pcb: FLIPPER_MAGSPOOF/mags.kicad_pcb
* src_file_repo_kicad_pcb_link: https://github.com/ElectronicCats/flipper-shields/tree/main/FLIPPER_MAGSPOOF/mags.kicad_pcb
* src_file_repo_kicad_sch: FLIPPER_MAGSPOOF/mags.kicad_sch
* src_file_repo_kicad_sch_link: https://github.com/ElectronicCats/flipper-shields/tree/main/FLIPPER_MAGSPOOF/mags.kicad_sch

* src_file_repo_sch: 
* src_file_repo_sch_link: https://github.com/ElectronicCats/flipper-shields/tree/main/
* full details link: https://github.com/oomlout/oomlout_oomp_project_bot_v_2/tree/main/projects/electroniccats_flipper_shields_mags/current_version/working

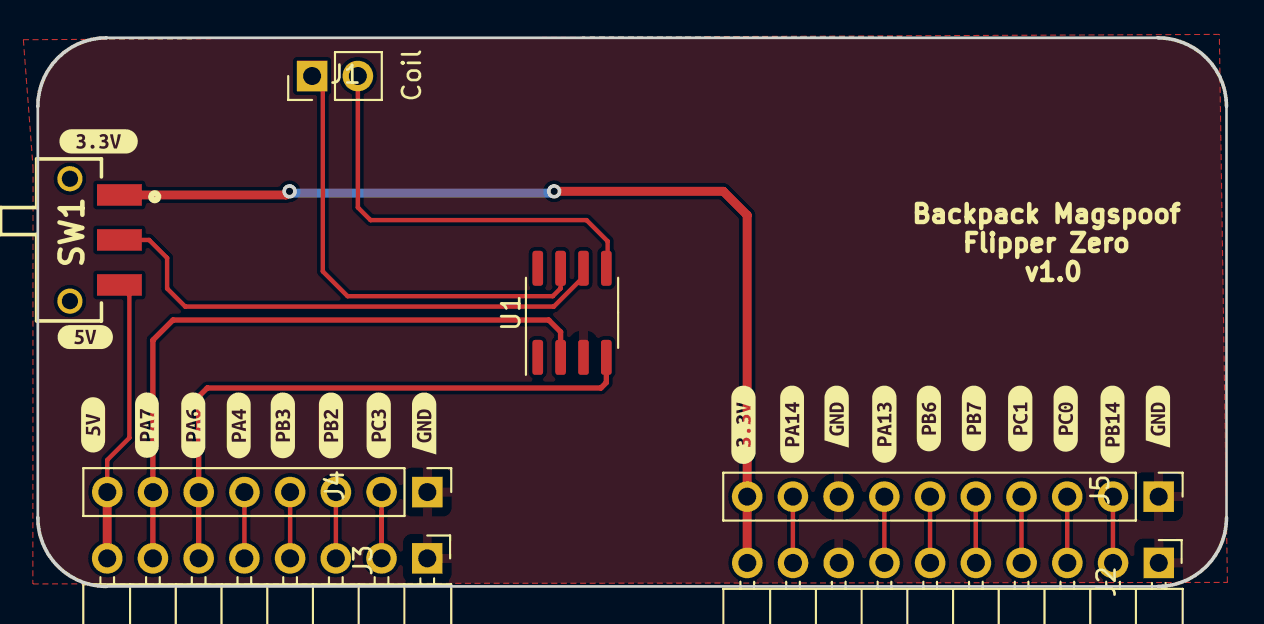
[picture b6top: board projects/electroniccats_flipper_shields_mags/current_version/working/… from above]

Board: 2 copper layers, 66.0 x 30.5 mm, 27 parts (0 on the bottom side), 19 nets.

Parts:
J1: Coil; PinHeader_1x02_P2.54mm_Vertical
J2: Conn_01x10_Socket; PinHeader_1x10_P2.54mm_Horizontal
J3: Conn_01x08_Socket; PinHeader_1x08_P2.54mm_Horizontal
J4: Conn_01x08_Socket; PinHeader_1x08_P2.54mm_Vertical
J5: Conn_01x10_Socket; PinHeader_1x10_P2.54mm_Vertical
SW1: On; JS102011SAQN
U1: TC4424; SOIC-8_3.9x4.9mm_P1.27mm
kibuzzard-648B91CB: G***; kibuzzard-648B91CB
kibuzzard-648B91E6: G***; kibuzzard-648B91E6
kibuzzard-648B91FC: G***; kibuzzard-648B91FC
kibuzzard-648B93B1: G***; kibuzzard-648B93B1
kibuzzard-648B93BF: G***; kibuzzard-648B93BF
kibuzzard-648B93D2: G***; kibuzzard-648B93D2
kibuzzard-648B93E0: G***; kibuzzard-648B93E0
kibuzzard-648B93EF: G***; kibuzzard-648B93EF
kibuzzard-648B921B: G***; kibuzzard-648B921B
kibuzzard-648B922F: G***; kibuzzard-648B922F
kibuzzard-648B923F: G***; kibuzzard-648B923F
kibuzzard-648B9401: G***; kibuzzard-648B9401
kibuzzard-648B9410: G***; kibuzzard-648B9410
kibuzzard-649DB344, kibuzzard-649DB344#2: G***; kibuzzard-649DB344
kibuzzard-6488EEAF, kibuzzard-6488EEAF#2, kibuzzard-6488EEAF#3: G***; kibuzzard-6488EEAF
kibuzzard-6488F75A, kibuzzard-6488F75A#2: G***; kibuzzard-6488F75A

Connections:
+3V3: J2.10 (Pin_1), J5.10 (Pin_1), SW1.1 (A)
+5V: J3.8 (Pin_1), J4.8 (Pin_1), SW1.3 (C)
/IN_A: J3.7 (Pin_2), J4.7 (Pin_2), U1.2 (IN_A)
/IN_B: J3.6 (Pin_3), J4.6 (Pin_3), U1.4 (IN_B)
/Out_A: J1.1, U1.7 (OUT_A)
/Out_B: J1.2, U1.5 (OUT_B)
/PA4: J3.5 (Pin_4), J4.5 (Pin_4)
/PA13: J2.7 (Pin_4), J5.7 (Pin_4)
/PA14: J2.9 (Pin_2), J5.9 (Pin_2)
/PB2: J3.3 (Pin_6), J4.3 (Pin_6)
/PB3: J3.4 (Pin_5), J4.4 (Pin_5)
/PB6: J2.6 (Pin_5), J5.6 (Pin_5)
/PB7: J2.5 (Pin_6), J5.5 (Pin_6)
/PB14: J2.2 (Pin_9), J5.2 (Pin_9)
/PC0: J2.3 (Pin_8), J5.3 (Pin_8)
/PC1: J2.4 (Pin_7), J5.4 (Pin_7)
/PC3: J3.2 (Pin_7), J4.2 (Pin_7)
/VDD: SW1.2 (B), U1.6 (VDD)
GND: J2.1 (Pin_10), J2.8 (Pin_3), J3.1 (Pin_8), J4.1 (Pin_8), J5.1 (Pin_10), J5.8 (Pin_3), U1.3 (GND)

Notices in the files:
projects/electroniccats_escornabot_makech_ogaki/current_version/working/working.kicad_pcb:
Attribution-ShareAlike 4.0 International (CC BY-SA 4.0)
